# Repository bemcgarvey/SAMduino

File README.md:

# SAMduino

## A demonstartion board for the ATSAMV71N21B microcontroller.  Includes firmware projects to demonstrate many modules and features.  
  
### There is sample firmware for:
* Basic gpio and interrupts
* DMA
* High speed USB
* QSPI with a SST26VF064B flash
* CAN-FD
* ADC and DAC
* PWM
* True random number generator
* TWI
* RTC
* USB bootloader
* High speed USB mass storage device with QSPI flash
* etc

### All firmware is built in MPLabX with MPLab Harmony 3 and the XC32 compiler.  
### Schematic and PCB were made with KiCAD

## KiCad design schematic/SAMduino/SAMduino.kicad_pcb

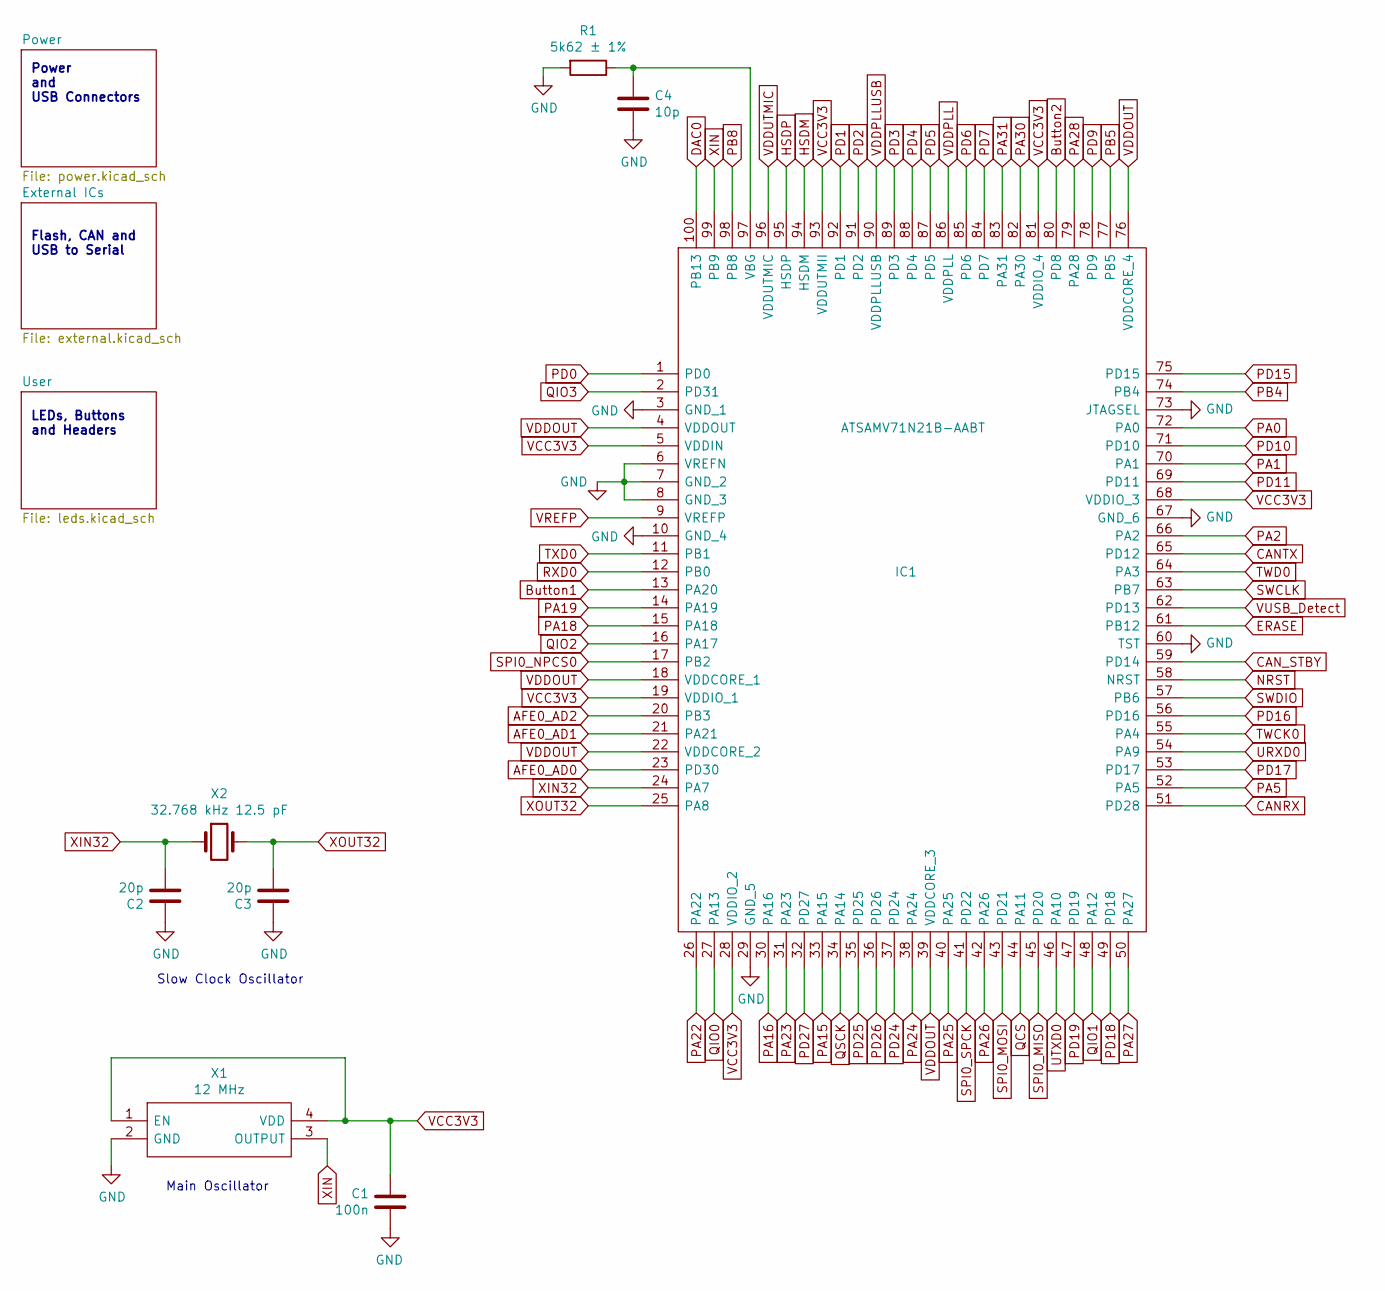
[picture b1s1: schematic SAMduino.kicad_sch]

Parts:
C1: 100n; C_0402_1005Metric
C2, C3: 20p; C_0603_1608Metric
C4: 10p; C_0603_1608Metric
IC1: ATSAMV71N21B-AABT; QFP50P1600X1600X160-100N; Mouser Part Number 556-ATSAMV71N21BAABT
R1: 5k62 ± 1%; R_0402_1005Metric
X1: 12 MHz; ASTMUPCE3312000MHZLJET
X2: 32.768 kHz 12.5 pF; CM9VT1A; Part Number CM9V-T1A-32.768kHz-12.5pF-20PPM-TA-QC; Mouser Part Number 428-202257-MC01

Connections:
AFE0_AD0: IC1.23 (PD30); also elsewhere on the board
AFE0_AD1: IC1.21 (PA21); also elsewhere on the board
AFE0_AD2: IC1.20 (PB3); also elsewhere on the board
Button1: IC1.13 (PA20); also elsewhere on the board
Button2: IC1.80 (PD8); also elsewhere on the board
CANRX: IC1.51 (PD28); also elsewhere on the board
CANTX: IC1.65 (PD12); also elsewhere on the board
CAN_STBY: IC1.59 (PD14); also elsewhere on the board
DAC0: IC1.100 (PB13); also elsewhere on the board
ERASE: IC1.61 (PB12); also elsewhere on the board
GND: C1.2, C2.1, C3.1, C4.2, IC1.3 (GND_1), IC1.6 (VREFN), IC1.7 (GND_2), IC1.8 (GND_3), IC1.10 (GND_4), IC1.29 (GND_5), IC1.60 (TST), IC1.67 (GND_6), IC1.73 (JTAGSEL), R1.2, X1.2 (GND); also elsewhere on the board
HSDM: IC1.94 (HSDM); also elsewhere on the board
HSDP: IC1.95 (HSDP); also elsewhere on the board
NRST: IC1.58 (NRST); also elsewhere on the board
unnamed: C4.1, IC1.97 (VBG), R1.1
PA0: IC1.72 (PA0); also elsewhere on the board
PA1: IC1.70 (PA1); also elsewhere on the board
PA2: IC1.66 (PA2); also elsewhere on the board
PA5: IC1.52 (PA5); also elsewhere on the board
PA15: IC1.33 (PA15); also elsewhere on the board
PA16: IC1.30 (PA16); also elsewhere on the board
PA18: IC1.15 (PA18); also elsewhere on the board
PA19: IC1.14 (PA19); also elsewhere on the board
PA22: IC1.26 (PA22); also elsewhere on the board
PA23: IC1.31 (PA23); also elsewhere on the board
PA24: IC1.38 (PA24); also elsewhere on the board
PA25: IC1.40 (PA25); also elsewhere on the board
PA26: IC1.42 (PA26); also elsewhere on the board
PA27: IC1.50 (PA27); also elsewhere on the board
PA28: IC1.79 (PA28); also elsewhere on the board
PA30: IC1.82 (PA30); also elsewhere on the board
PA31: IC1.83 (PA31); also elsewhere on the board
PB4: IC1.74 (PB4); also elsewhere on the board
PB5: IC1.77 (PB5); also elsewhere on the board
PB8: IC1.98 (PB8); also elsewhere on the board
PD0: IC1.1 (PD0); also elsewhere on the board
PD1: IC1.92 (PD1); also elsewhere on the board
PD2: IC1.91 (PD2); also elsewhere on the board
PD3: IC1.89 (PD3); also elsewhere on the board
PD4: IC1.88 (PD4); also elsewhere on the board
PD5: IC1.87 (PD5); also elsewhere on the board
PD6: IC1.85 (PD6); also elsewhere on the board
PD7: IC1.84 (PD7); also elsewhere on the board
PD9: IC1.78 (PD9); also elsewhere on the board
PD10: IC1.71 (PD10); also elsewhere on the board
PD11: IC1.69 (PD11); also elsewhere on the board
PD15: IC1.75 (PD15); also elsewhere on the board
PD16: IC1.56 (PD16); also elsewhere on the board
PD17: IC1.53 (PD17); also elsewhere on the board
PD18: IC1.49 (PD18); also elsewhere on the board
PD19: IC1.47 (PD19); also elsewhere on the board
PD24: IC1.37 (PD24); also elsewhere on the board
PD25: IC1.35 (PD25); also elsewhere on the board
PD26: IC1.36 (PD26); also elsewhere on the board
PD27: IC1.32 (PD27); also elsewhere on the board
QCS: IC1.44 (PA11); also elsewhere on the board
QIO0: IC1.27 (PA13); also elsewhere on the board
QIO1: IC1.48 (PA12); also elsewhere on the board
QIO2: IC1.16 (PA17); also elsewhere on the board
QIO3: IC1.2 (PD31); also elsewhere on the board
QSCK: IC1.34 (PA14); also elsewhere on the board
RXD0: IC1.12 (PB0); also elsewhere on the board
SPI0_MISO: IC1.45 (PD20); also elsewhere on the board
SPI0_MOSI: IC1.43 (PD21); also elsewhere on the board
SPI0_NPCS0: IC1.17 (PB2); also elsewhere on the board
SPI0_SPCK: IC1.41 (PD22); also elsewhere on the board
SWCLK: IC1.63 (PB7); also elsewhere on the board
SWDIO: IC1.57 (PB6); also elsewhere on the board
TWCK0: IC1.55 (PA4); also elsewhere on the board
TWD0: IC1.64 (PA3); also elsewhere on the board
TXD0: IC1.11 (PB1); also elsewhere on the board
URXD0: IC1.54 (PA9); also elsewhere on the board
UTXD0: IC1.46 (PA10); also elsewhere on the board
VCC3V3: C1.1, IC1.5 (VDDIN), IC1.19 (VDDIO_1), IC1.28 (VDDIO_2), IC1.68 (VDDIO_3), IC1.81 (VDDIO_4), IC1.93 (VDDUTMII), X1.1 (EN), X1.4 (VDD); also elsewhere on the board
VDDOUT: IC1.4 (VDDOUT), IC1.18 (VDDCORE_1), IC1.22 (VDDCORE_2), IC1.39 (VDDCORE_3), IC1.76 (VDDCORE_4); also elsewhere on the board
VDDPLL: IC1.86 (VDDPLL); also elsewhere on the board
VDDPLLUSB: IC1.90 (VDDPLLUSB); also elsewhere on the board
VDDUTMIC: IC1.96 (VDDUTMIC); also elsewhere on the board
VREFP: IC1.9 (VREFP); also elsewhere on the board
VUSB_Detect: IC1.62 (PD13); also elsewhere on the board
XIN: IC1.99 (PB9), X1.3 (OUTPUT)
XIN32: C2.2, IC1.24 (PA7), X2.1
XOUT32: C3.2, IC1.25 (PA8), X2.2

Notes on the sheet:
Main Oscillator
Flash, CAN and USB to Serial
LEDs, Buttons and Headers
Slow Clock Oscillator
Power and USB Connectors

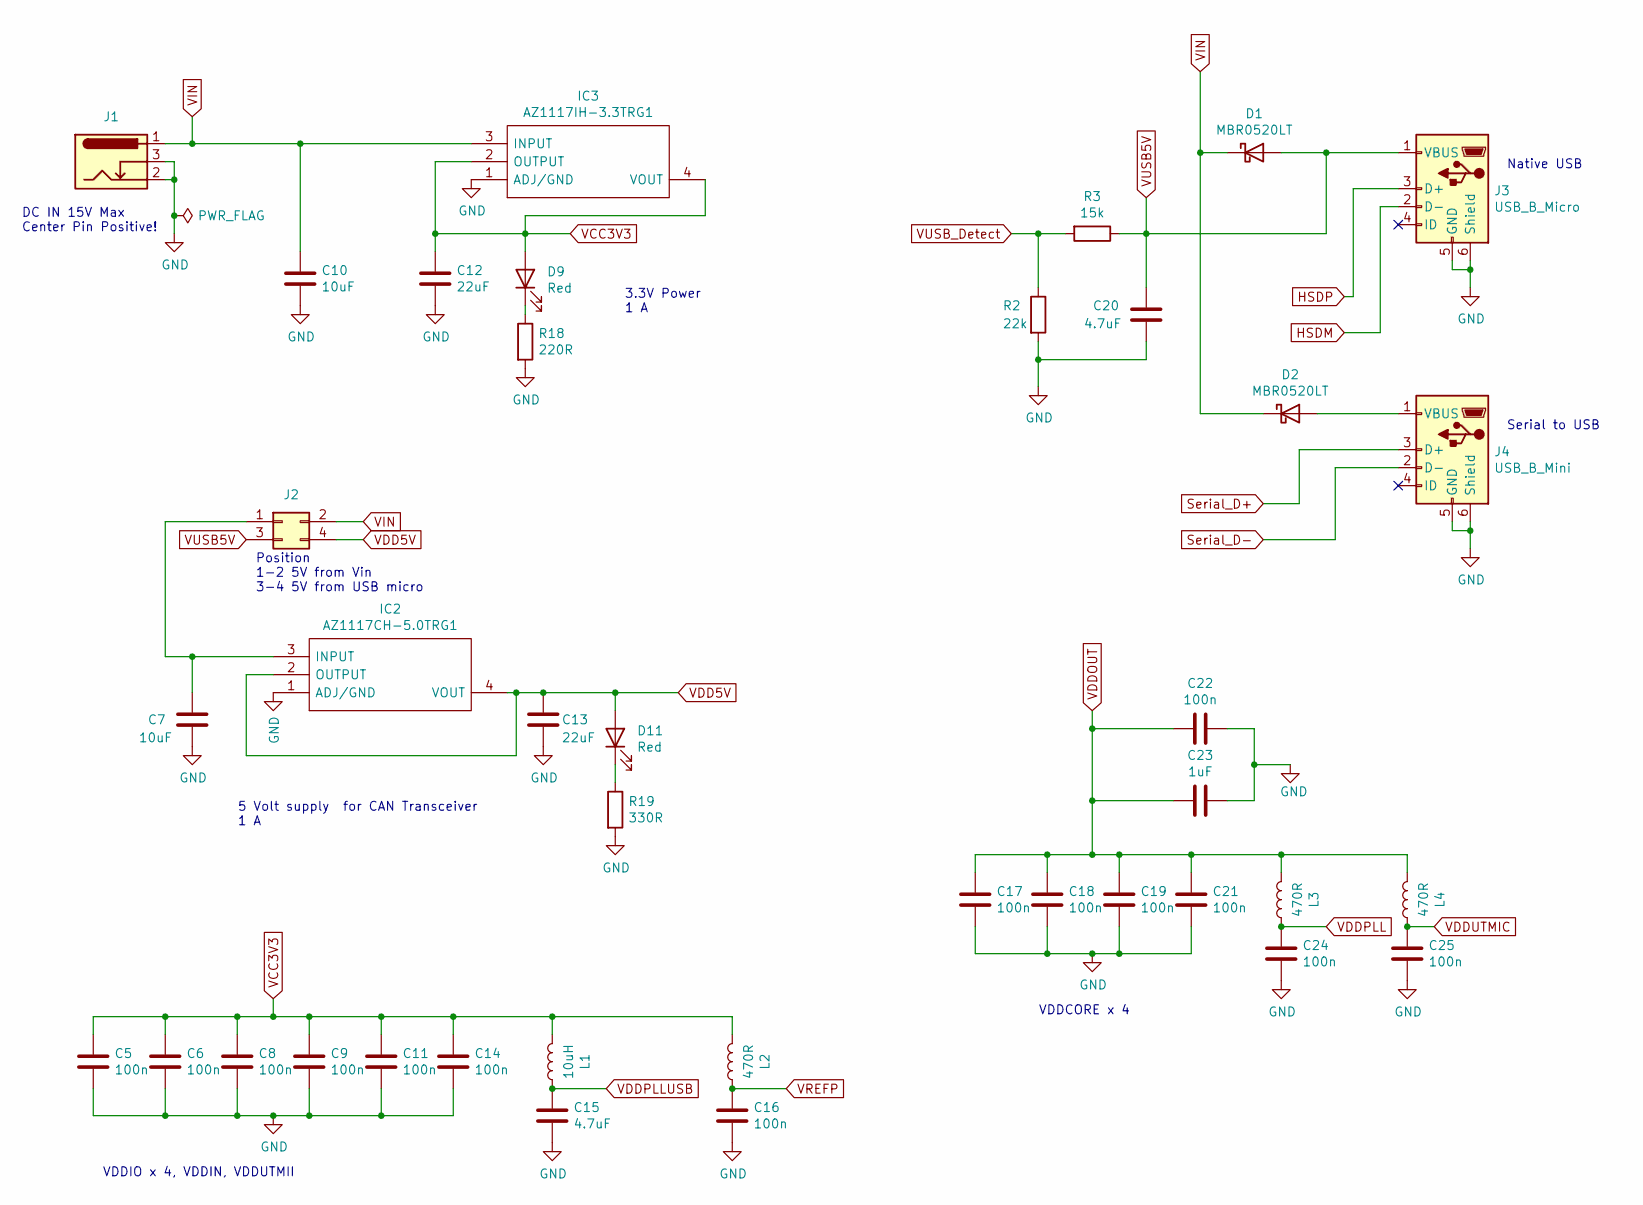
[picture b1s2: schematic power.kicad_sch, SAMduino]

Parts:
C5, C6, C8, C9, C11, C14, C16, C17, C18, C19, C21, C22, C24, C25: 100n; C_0402_1005Metric
C7, C10: 10uF; C_0805_2012Metric
C12, C13: 22uF; C_0603_1608Metric
C15, C20: 4.7uF; C_0603_1608Metric
C23: 1uF; C_0402_1005Metric
D1, D2: MBR0520LT; D_SOD-123
D9, D11: Red; LED_0603_1608Metric
IC2: AZ1117CH-5.0TRG1; SOT230P700X180-4N; Mouser Part Number 621-AZ1117CH-5.0TRG1
IC3: AZ1117IH-3.3TRG1; SOT230P700X180-4N; Mouser Part Number 621-AZ1117IH-3.3TRG1
J1: Barrel_Jack_Switch; BarrelJack_Wuerth_6941xx301002
J2: Conn_02x02_Odd_Even; PinHeader_2x02_P2.54mm_Vertical
J3: USB_B_Micro; USB_Micro-B_Amphenol_10104110_Horizontal
J4: USB_B_Mini; USB_Mini-B_Wuerth_65100516121_Horizontal
L1: 10uH; L_0603_1608Metric
L2, L3, L4: 470R; L_0603_1608Metric
R2: 22k; R_0603_1608Metric
R3: 15k; R_0603_1608Metric
R18: 220R; R_0603_1608Metric
R19: 330R; R_0603_1608Metric

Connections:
GND: C5.2, C6.2, C7.2, C8.2, C9.2, C10.2, C11.2, C12.2, C13.2, C14.2, C15.2, C16.2, C17.2, C18.2, C19.2, C20.2, C21.2, C22.1, C23.1, C24.2, C25.2, IC2.1 (ADJ/GND), IC3.1 (ADJ/GND), J1.2, J1.3, J3.5 (GND), J3.6 (Shield), J4.5 (GND), J4.6 (Shield), R2.2, R18.2, R19.2; also elsewhere on the board
HSDM: J3.2 (D-); also elsewhere on the board
HSDP: J3.3 (D+); also elsewhere on the board
unnamed: C7.1, IC2.3 (INPUT), J2.1
unnamed: D2.2 (A), J4.1 (VBUS)
unnamed: D9.1 (K), R18.1
unnamed: D11.1 (K), R19.1
Serial_D+: J4.3 (D+); also elsewhere on the board
Serial_D-: J4.2 (D-); also elsewhere on the board
VCC3V3: C5.1, C6.1, C8.1, C9.1, C11.1, C12.1, C14.1, D9.2 (A), IC3.2 (OUTPUT), IC3.4 (VOUT), L1.2, L2.2; also elsewhere on the board
VDD5V: C13.1, D11.2 (A), IC2.2 (OUTPUT), IC2.4 (VOUT), J2.4; also elsewhere on the board
VDDOUT: C17.1, C18.1, C19.1, C21.1, C22.2, C23.2, L3.2, L4.2; also elsewhere on the board
VDDPLL: C24.1, L3.1; also elsewhere on the board
VDDPLLUSB: C15.1, L1.1; also elsewhere on the board
VDDUTMIC: C25.1, L4.1; also elsewhere on the board
VIN: C10.1, D1.1 (K), D2.1 (K), IC3.3 (INPUT), J1.1, J2.2; also elsewhere on the board
VREFP: C16.1, L2.1; also elsewhere on the board
VUSB5V: C20.1, D1.2 (A), J2.3, J3.1 (VBUS), R3.1
VUSB_Detect: R2.1, R3.2; also elsewhere on the board

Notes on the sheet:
Serial to USB
Position 1-2 5V from Vin 3-4 5V from USB micro
DC IN 15V Max Center Pin Positive!
VDDIO x 4, VDDIN, VDDUTMII
VDDCORE x 4
3.3V Power 1 A
5 Volt supply for CAN Transceiver 1 A
Native USB

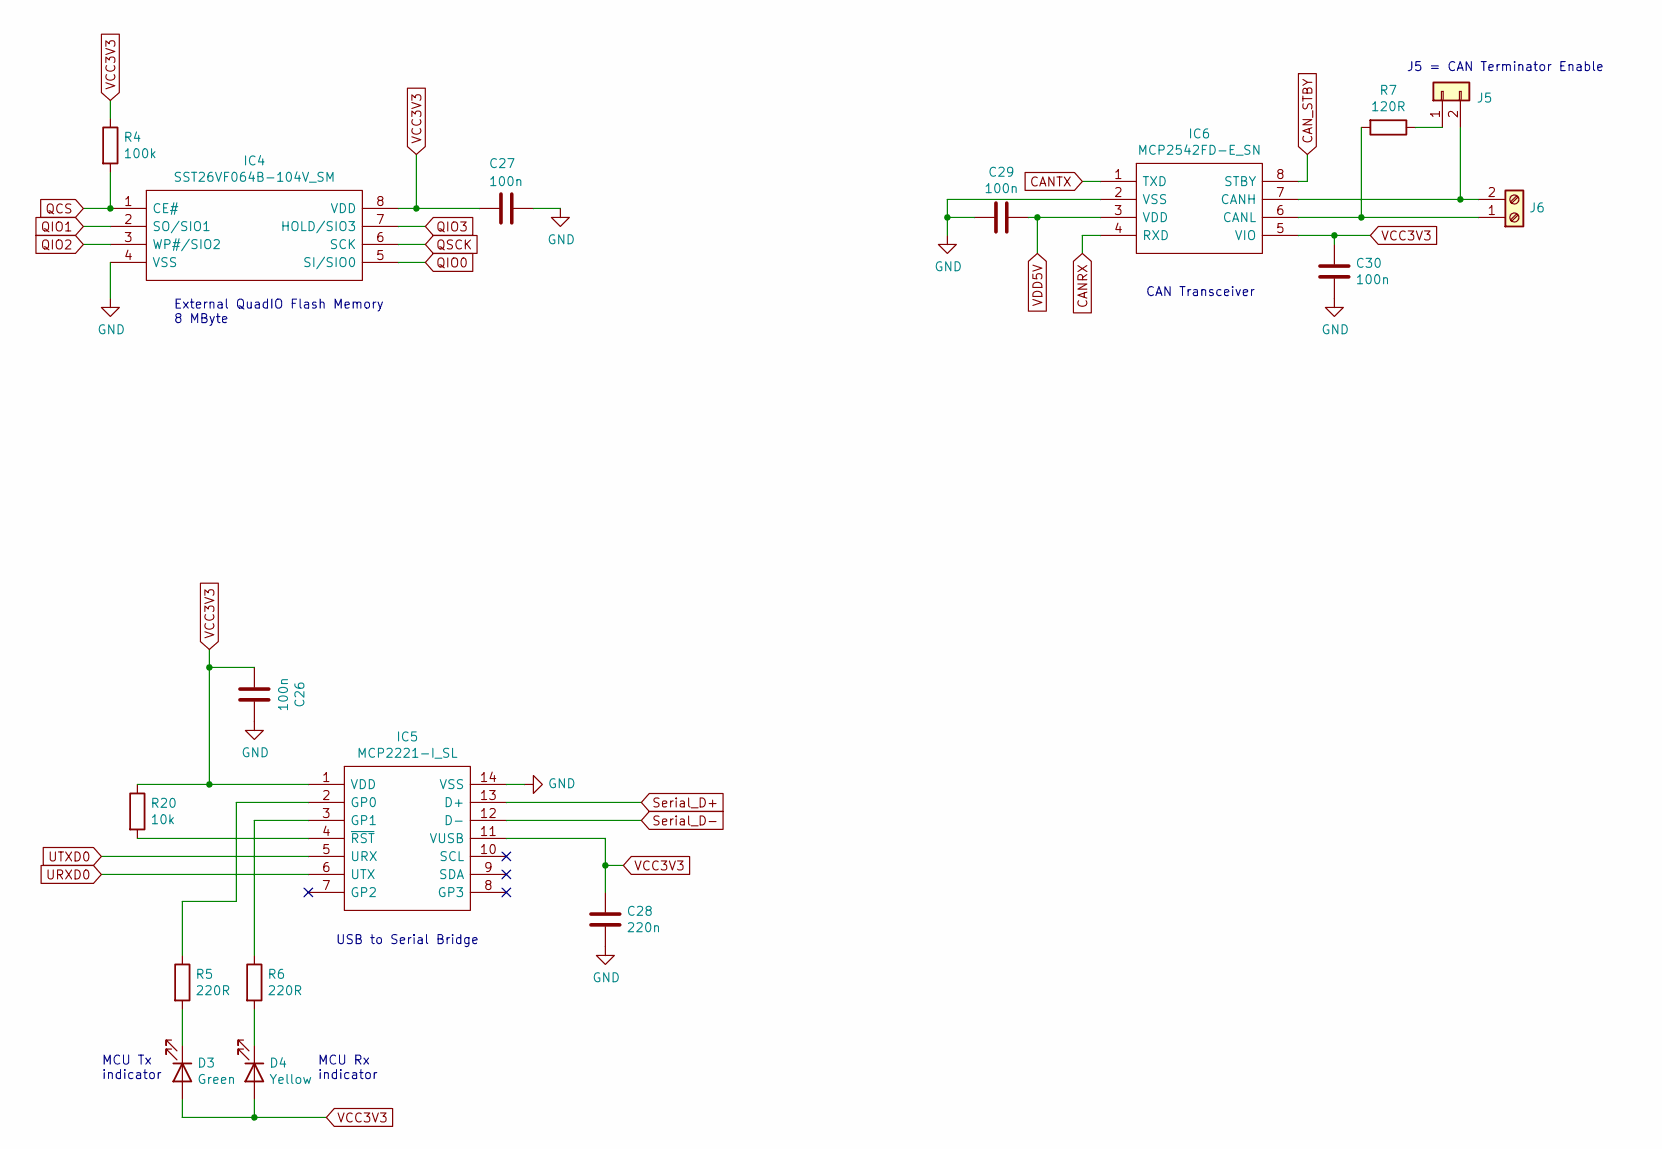
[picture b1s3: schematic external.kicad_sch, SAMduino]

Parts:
C26, C27, C29, C30: 100n; C_0603_1608Metric
C28: 220n; C_0603_1608Metric
D3: Green; LED_0603_1608Metric
D4: Yellow; LED_0603_1608Metric
IC4: SST26VF064B-104V_SM; SOIC127P794X203-8N; Mouser Part Number 579-26VF064B-104V/SM
IC5: MCP2221-I_SL; SOIC127P600X175-14N; Mouser Part Number 579-MCP2221-I/SL
IC6: MCP2542FD-E_SN; SOIC127P600X175-8N; Mouser Part Number 579-MCP2542FD-E/SN
J5: Conn_01x02; PinHeader_1x02_P2.54mm_Vertical
J6: Screw_Terminal_01x02; 1725656
R4: 100k; R_0603_1608Metric
R5, R6: 220R; R_0603_1608Metric
R7: 120R; R_0805_2012Metric
R20: 10k; R_0603_1608Metric

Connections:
CANRX: IC6.4 (RXD); also elsewhere on the board
CANTX: IC6.1 (TXD); also elsewhere on the board
CAN_STBY: IC6.8 (STBY); also elsewhere on the board
GND: C26.1, C27.1, C28.2, C29.1, C30.2, IC4.4 (VSS), IC5.14 (VSS), IC6.2 (VSS); also elsewhere on the board
unnamed: D3.1 (K), R5.2
unnamed: D4.1 (K), R6.2
unnamed: IC5.2 (GP0), R5.1
unnamed: IC5.3 (GP1), R6.1
unnamed: IC5.4 (~RST), R20.2
unnamed: IC6.6 (CANL), J6.1, R7.2
unnamed: IC6.7 (CANH), J5.2, J6.2
unnamed: J5.1, R7.1
QCS: IC4.1 (CE#), R4.2; also elsewhere on the board
QIO0: IC4.5 (SI/SIO0); also elsewhere on the board
QIO1: IC4.2 (SO/SIO1); also elsewhere on the board
QIO2: IC4.3 (WP#/SIO2); also elsewhere on the board
QIO3: IC4.7 (HOLD/SIO3); also elsewhere on the board
QSCK: IC4.6 (SCK); also elsewhere on the board
Serial_D+: IC5.13 (D+); also elsewhere on the board
Serial_D-: IC5.12 (D-); also elsewhere on the board
URXD0: IC5.6 (UTX); also elsewhere on the board
UTXD0: IC5.5 (URX); also elsewhere on the board
VCC3V3: C26.2, C27.2, C28.1, C30.1, D3.2 (A), D4.2 (A), IC4.8 (VDD), IC5.1 (VDD), IC5.11 (VUSB), IC6.5 (VIO), R4.1, R20.1; also elsewhere on the board
VDD5V: C29.2, IC6.3 (VDD); also elsewhere on the board

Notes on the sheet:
USB to Serial Bridge
MCU Tx indicator
External QuadIO Flash Memory 8 MByte
MCU Rx indicator
J5 = CAN Terminator Enable
CAN Transceiver

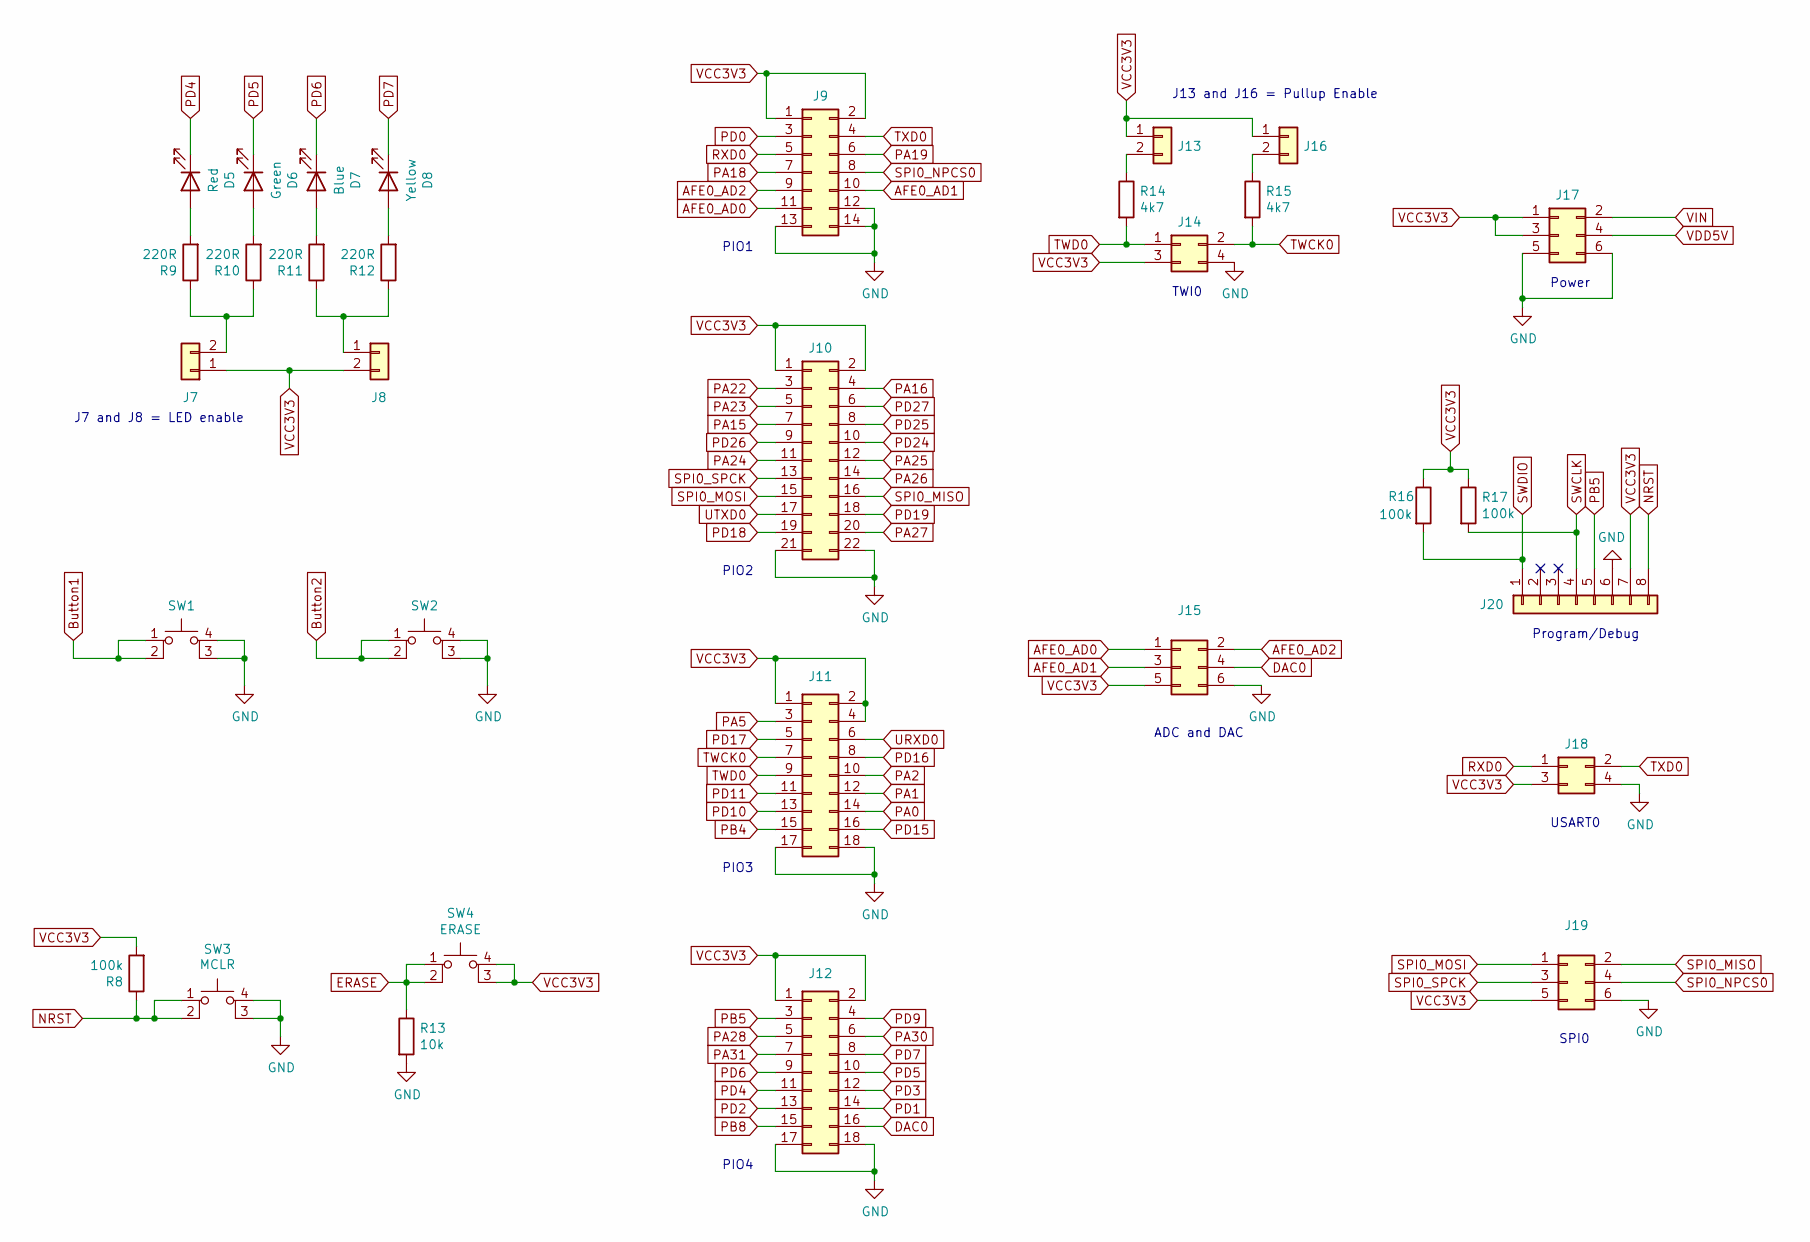
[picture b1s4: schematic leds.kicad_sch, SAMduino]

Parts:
D5: Red; LED_0805_2012Metric
D6: Green; LED_0805_2012Metric
D7: Blue; LED_0805_2012Metric
D8: Yellow; LED_0805_2012Metric
J7, J8, J13, J16: Conn_01x02; PinHeader_1x02_P2.54mm_Vertical
J9: Conn_02x07_Odd_Even; PinHeader_2x07_P2.54mm_Vertical
J10: Conn_02x11_Odd_Even; PinHeader_2x11_P2.54mm_Vertical
J11, J12: Conn_02x09_Odd_Even; PinHeader_2x09_P2.54mm_Vertical
J14, J18: Conn_02x02_Odd_Even; PinHeader_2x02_P2.54mm_Vertical
J15, J17, J19: Conn_02x03_Odd_Even; PinHeader_2x03_P2.54mm_Vertical
J20: Conn_01x08; PinHeader_1x08_P2.54mm_Horizontal
R8, R16, R17: 100k; R_0603_1608Metric
R9, R10, R11, R12: 220R; R_0603_1608Metric
R13: 10k; R_0603_1608Metric
R14, R15: 4k7; R_0603_1608Metric
SW1, SW2: SW_MEC_5E; FSM16JH
SW3: MCLR; PTS647SK38SMTR2LFS
SW4: ERASE; PTS647SK38SMTR2LFS

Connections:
AFE0_AD0: J9.11, J15.1; also elsewhere on the board
AFE0_AD1: J9.10, J15.3; also elsewhere on the board
AFE0_AD2: J9.9, J15.2; also elsewhere on the board
Button1: SW1.1, SW1.2; also elsewhere on the board
Button2: SW2.1, SW2.2; also elsewhere on the board
DAC0: J12.16, J15.4; also elsewhere on the board
ERASE: R13.1, SW4.1, SW4.2; also elsewhere on the board
GND: J9.12, J9.13, J9.14, J10.21, J10.22, J11.17, J11.18, J12.17, J12.18, J14.4, J15.6, J17.5, J17.6, J18.4, J19.6, J20.6, R13.2, SW1.3 (K), SW1.4 (A), SW2.3 (K), SW2.4 (A), SW3.3 (K), SW3.4 (A); also elsewhere on the board
NRST: J20.8, R8.1, SW3.1, SW3.2; also elsewhere on the board
unnamed: D5.2 (A), R9.2
unnamed: D6.2 (A), R10.2
unnamed: D7.2 (A), R11.2
unnamed: D8.2 (A), R12.2
unnamed: J7.2, R9.1, R10.1
unnamed: J8.1, R11.1, R12.1
unnamed: J13.2, R14.1
unnamed: J16.2, R15.1
PA0: J11.14; also elsewhere on the board
PA1: J11.12; also elsewhere on the board
PA2: J11.10; also elsewhere on the board
PA5: J11.3; also elsewhere on the board
PA15: J10.7; also elsewhere on the board
PA16: J10.4; also elsewhere on the board
PA18: J9.7; also elsewhere on the board
PA19: J9.6; also elsewhere on the board
PA22: J10.3; also elsewhere on the board
PA23: J10.5; also elsewhere on the board
PA24: J10.11; also elsewhere on the board
PA25: J10.12; also elsewhere on the board
PA26: J10.14; also elsewhere on the board
PA27: J10.20; also elsewhere on the board
PA28: J12.5; also elsewhere on the board
PA30: J12.6; also elsewhere on the board
PA31: J12.7; also elsewhere on the board
PB4: J11.15; also elsewhere on the board
PB5: J12.3, J20.5; also elsewhere on the board
PB8: J12.15; also elsewhere on the board
PD0: J9.3; also elsewhere on the board
PD1: J12.14; also elsewhere on the board
PD2: J12.13; also elsewhere on the board
PD3: J12.12; also elsewhere on the board
PD4: D5.1 (K), J12.11; also elsewhere on the board
PD5: D6.1 (K), J12.10; also elsewhere on the board
PD6: D7.1 (K), J12.9; also elsewhere on the board
PD7: D8.1 (K), J12.8; also elsewhere on the board
PD9: J12.4; also elsewhere on the board
PD10: J11.13; also elsewhere on the board
PD11: J11.11; also elsewhere on the board
PD15: J11.16; also elsewhere on the board
PD16: J11.8; also elsewhere on the board
PD17: J11.5; also elsewhere on the board
PD18: J10.19; also elsewhere on the board
PD19: J10.18; also elsewhere on the board
PD24: J10.10; also elsewhere on the board
PD25: J10.8; also elsewhere on the board
PD26: J10.9; also elsewhere on the board
PD27: J10.6; also elsewhere on the board
RXD0: J9.5, J18.1; also elsewhere on the board
SPI0_MISO: J10.16, J19.2; also elsewhere on the board
SPI0_MOSI: J10.15, J19.1; also elsewhere on the board
SPI0_NPCS0: J9.8, J19.4; also elsewhere on the board
SPI0_SPCK: J10.13, J19.3; also elsewhere on the board
SWCLK: J20.4, R17.2; also elsewhere on the board
SWDIO: J20.1, R16.2; also elsewhere on the board
TWCK0: J11.7, J14.2, R15.2; also elsewhere on the board
TWD0: J11.9, J14.1, R14.2; also elsewhere on the board
TXD0: J9.4, J18.2; also elsewhere on the board
URXD0: J11.6; also elsewhere on the board
UTXD0: J10.17; also elsewhere on the board
VCC3V3: J7.1, J8.2, J9.1, J9.2, J10.1, J10.2, J11.1, J11.2, J11.4, J12.1, J12.2, J13.1, J14.3, J15.5, J16.1, J17.1, J17.3, J18.3, J19.5, J20.7, R8.2, R16.1, R17.1, SW4.3 (K), SW4.4 (A); also elsewhere on the board
VDD5V: J17.4; also elsewhere on the board
VIN: J17.2; also elsewhere on the board

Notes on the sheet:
J7 and J8 = LED enable
SPI0
PIO1
TWI0
PIO2
PIO3
Power
ADC and DAC
PIO4
USART0
Program/Debug
J13 and J16 = Pullup Enable

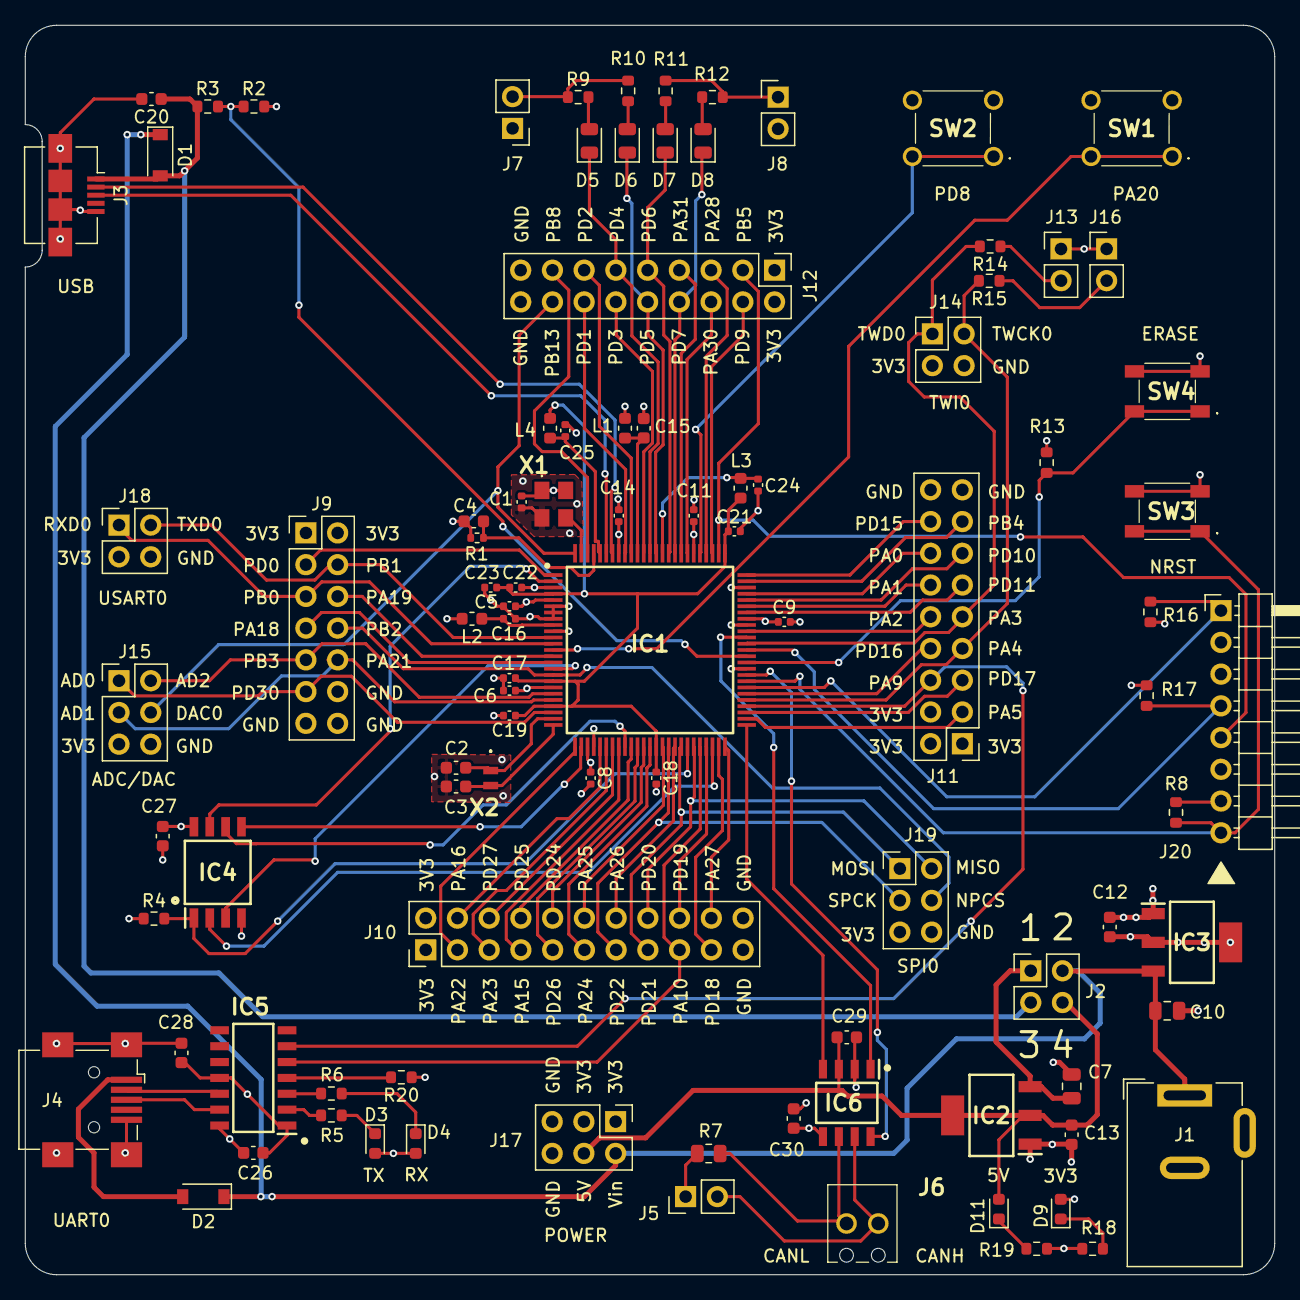
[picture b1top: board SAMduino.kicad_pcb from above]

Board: 4 copper layers, 100.0 x 100.0 mm, 96 parts (0 on the bottom side), 108 nets.

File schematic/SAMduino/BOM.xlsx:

Reference | Quantity | Value | Footprint
C1 C5 C6 C8 C9 C11 C14 C16 C17 C18 C19 C21 C22 C24 C25 | 15 | 100n | Capacitor_SMD:C_0402_1005Metric
C7 C10 | 2 | 10uF | Capacitor_SMD:C_0805_2012Metric
C12 C13 | 2 | 22uF | Capacitor_SMD:C_0603_1608Metric
C15 C20 | 2 | 4.7uF | Capacitor_SMD:C_0603_1608Metric
C23 | 1 | 1uF | Capacitor_SMD:C_0402_1005Metric
C28 | 1 | 220n | Capacitor_SMD:C_0603_1608Metric
C2 C3 | 2 | 20p | Capacitor_SMD:C_0603_1608Metric
C26 C27 C29 C30 | 4 | 100n | Capacitor_SMD:C_0603_1608Metric
C4 | 1 | 10p | Capacitor_SMD:C_0603_1608Metric
D1 D2 | 2 | MBR0520LT | Diode_SMD:D_SOD-123
D3 | 1 | Green | LED_SMD:LED_0603_1608Metric
D4 | 1 | Yellow | LED_SMD:LED_0603_1608Metric
D5 | 1 | Red | LED_SMD:LED_0805_2012Metric
D6 | 1 | Green | LED_SMD:LED_0805_2012Metric
D7 | 1 | Blue | LED_SMD:LED_0805_2012Metric
D8 | 1 | Yellow | LED_SMD:LED_0805_2012Metric
D9 D11 | 2 | Red | LED_SMD:LED_0603_1608Metric
IC1 | 1 | ATSAMV71N21B-AABT | SamacSys_Parts:QFP50P1600X1600X160-100N
IC2 | 1 | AZ1117CH-5.0TRG1 | SOT230P700X180-4N
IC3 | 1 | AZ1117IH-3.3TRG1 | SOT230P700X180-4N
IC4 | 1 | SST26VF064B-104V_SM | SamacSys_Parts:SOIC127P794X203-8N
IC5 | 1 | MCP2221-I_SL | SamacSys_Parts:SOIC127P600X175-14N
IC6 | 1 | MCP2542FD-E_SN | SamacSys_Parts:SOIC127P600X175-8N
J1 | 1 | Barrel_Jack_Switch | Connector_BarrelJack:BarrelJack_Wuerth_6941xx301002
J10 | 1 | Conn_02x11_Odd_Even | Connector_PinHeader_2.54mm:PinHeader_2x11_P2.54mm_Vertical
J11 J12 | 2 | Conn_02x09_Odd_Even | Connector_PinHeader_2.54mm:PinHeader_2x09_P2.54mm_Vertical
J15 J17 J19 | 3 | Conn_02x03_Odd_Even | Connector_PinHeader_2.54mm:PinHeader_2x03_P2.54mm_Vertical
J2 J14 J18 | 3 | Conn_02x02_Odd_Even | Connector_PinHeader_2.54mm:PinHeader_2x02_P2.54mm_Vertical
J20 | 1 | Conn_01x08 | Connector_PinHeader_2.54mm:PinHeader_1x08_P2.54mm_Horizontal
J3 | 1 | USB_B_Micro | Connector_USB:USB_Micro-B_Amphenol_10104110_Horizontal
J4 | 1 | USB_B_Mini | Connector_USB:USB_Mini-B_Wuerth_65100516121_Horizontal
J5 J7 J8 J13 J16 | 5 | Conn_01x02 | Connector_PinHeader_2.54mm:PinHeader_1x02_P2.54mm_Vertical
J6 | 1 | Screw_Terminal_01x02 | SamacSys_Parts:1725656
J9 | 1 | Conn_02x07_Odd_Even | Connector_PinHeader_2.54mm:PinHeader_2x07_P2.54mm_Vertical
L1 | 1 | 10uH | Inductor_SMD:L_0603_1608Metric
L2 L3 L4 | 3 | 470R | Inductor_SMD:L_0603_1608Metric
R1 | 1 | 5k62 ± 1% | Resistor_SMD:R_0402_1005Metric
R14 R15 | 2 | 4k7 | Resistor_SMD:R_0603_1608Metric
R5 R6 R9 R10 R11 R12 R18 | 7 | 220R | Resistor_SMD:R_0603_1608Metric
R19 | 1 | 330R | Resistor_SMD:R_0603_1608Metric
R2 | 1 | 22k | Resistor_SMD:R_0603_1608Metric
R13 R20 | 2 | 10k | Resistor_SMD:R_0603_1608Metric
R3 | 1 | 15k | Resistor_SMD:R_0603_1608Metric
R4 R8 R16 R17 | 4 | 100k | Resistor_SMD:R_0603_1608Metric
R7 | 1 | 120R | Resistor_SMD:R_0805_2012Metric
SW1 SW2 | 2 | SW_MEC_5E | SamacSys_Parts:FSM16JH
SW3 | 1 | MCLR | SamacSys_Parts:PTS647SK38SMTR2LFS
SW4 | 1 | ERASE | SamacSys_Parts:PTS647SK38SMTR2LFS
X1 | 1 | 12 MHz | SamacSys_Parts:ASTMUPCE3312000MHZLJET
X2 | 1 | 32.768 kHz 12.5 pF | SamacSys_Parts:CM9VT1A

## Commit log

2021-10-08 Initial Kicad project
2021-10-10 Partial schematic
2021-10-11 Specialty pins wired
2021-10-12 All pins connected
2021-10-14 Schematic with footprints
    Some footprints need to be verified with actual components
2021-10-15 Ready for PCB
2021-10-15 Start of pcb layout. Rules set.
2021-10-15 Almost routed - first attempt
2021-10-15 Changed MCP2221 RST connection
    Removed some comments
2021-10-15 PCB routed - needs optimization
2021-10-16 Some silkscreen done
    Prior to swapping ICSP pins
2021-10-16 Swapped program header to match PicKit4
2021-10-16 Full PCB layout
2021-10-16 Minor fixes to PCB
2021-10-16 Updated BOM
2021-10-17 Generated gerbers
2021-10-18 Minor PCB improvements
2021-10-18 Changed oscillator to 3.2x2.5 size
2021-10-19 Changed gerber parameters
    Set to JLPCB suggested values
2021-10-19 Updated gerber settings
2021-10-21 Changed voltage regulators
2021-10-22 Removed D10
2021-10-22 Final gerbers
2021-10-23 Changed via size
2021-10-23 Finalized schematic V1.0
2021-10-27 Initial Harmony project
2021-11-12 Fixed button labels on silkscreen
2021-11-12 Buttons and LEDs tested.
    Running code with internal oscillator
2021-11-12 Oscillators tested and working
2021-11-13 UART0 and timer tested
2021-11-13 Different timer clocks
2021-11-13 Changed firmware directory structure
2021-11-13 Working CDC demo - High Speed USB
2021-11-14 Fixed CAN connector labels and added errata
2021-11-15 Initial SQI code - not all working
2021-11-15 Initial TWI code with LCD
2021-11-15 TWI with LCD working
    Except for LCDReadLine()
2021-11-17 Fresh start on QSPI
2021-11-18 Got SQI working
2021-11-19 Full Demo code - Menu, buttons and leds working
2021-11-20 SQI flash demo working
2021-11-20 CAN Tx working
2021-11-21 CAN RX working (no interrupts)
2021-11-21 CAN interrupts working
2021-11-21 Removed test projects
    These are now included in FullDemo
2021-11-22 TWI with LCD working
    Removed proof of concept files
2021-11-22 Changed some comments
2021-11-22 TRNG working
    Also organized Harmony components in groups
2021-11-22 Reorganized Harmony groups
2021-11-22 RTC working
2021-11-23 ADC working
2021-11-23 Added SAMV71 errata
2021-11-23 Enabled instruction cache
    Data cache is still causing problems with qspi
2021-11-23 Solved QSPI problem with cache
2021-11-23 DAC working
2021-11-24 USB enumerates.
2021-11-24 Adjusted task and interrupt priorities
2021-11-24 USB attach and detach working
2021-11-24 Mouse is working
2021-11-24 Removed test project
2021-11-25 USB HID idle time working
2021-11-25 Changed UART RX to interrupt instead of task
2021-11-25 Adjusted interrupt priorities
2021-11-26 Changed drive strength on LED pins
2021-11-28 PWM working
2021-12-02 Added MSD with SQI flash demo
2021-12-02 Fixed config errors
2021-12-03 Changed MPU settings for QSPI
2021-12-03 Added file system to MSD demo
2021-12-03 Removed/renamed some docs
2021-12-03 Updated notes
2021-12-03 Added functionality to MSD demo
2021-12-04 Initial DMA demo
2021-12-04 DMA demo working
2021-12-06 Added USB bootloader demo
2021-12-07 Switched to SYS_TIME for lcd delay
2021-12-07 Moved DAC timer to TC0 - removed TC3
2021-12-08 Changed TC0 to TC1
    To allow TC0 to be used for quadrature decoder
2021-12-08 Added quadrature encoder
2021-12-10 Improvements to hid bootloader
2021-12-12 Fixed month value
2021-12-15 Added non-contiguous function to test bootloaders
2021-12-23 Updated PIDs
2021-12-29 Changed msd manufacturer string
2021-12-30 Fixed manifest
2022-01-19 Converted to KiCad 6
